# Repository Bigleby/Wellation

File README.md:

# Wellation
Solderingstation with 2 Ports for Weller RT soldering irons.

This Project is in Progress...
Status: A.0 PCBs ordered

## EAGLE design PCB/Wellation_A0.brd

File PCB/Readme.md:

Created with Eagle 7.6.0

Schematic: Wellation_A

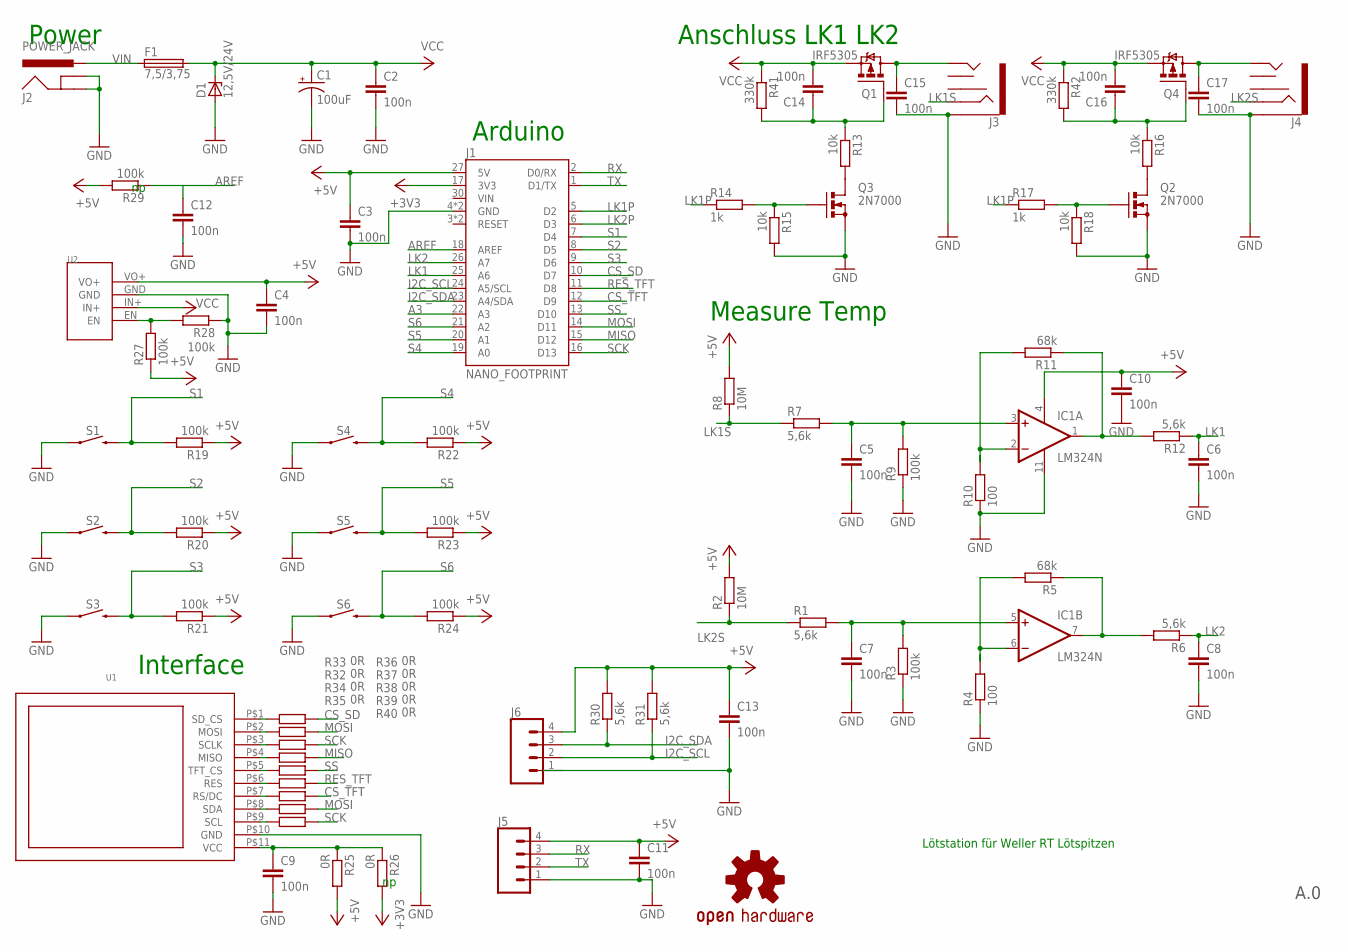
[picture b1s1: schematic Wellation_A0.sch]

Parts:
C1: 100uF; CPOL-RADIAL-2.5MM-6.5MM
C2, C3, C4, C5, C6, C7, C8, C9, C10, C11, C12, C13, C14, C15, C16, C17: 100n; C0603K
D1: 12,5V/24V; ZDIO12.5
F1: 7,5/3,75; GSH15
IC1: LM324N; DIL14
J1: NANO_FOOTPRINT; NANO
J2: POWER_JACK; POWER_JACK_PTH
J3, J4: AUDIO_JACK_3.5MM_PTH; AUDIO-JACK
J5, J6: CONN_04JST-PTH-VERT; JST-4-PTH-VERT
LOGO1: OSHW-LOGOM-COPPER; OSHW-LOGO-M_COPPER
Q1, Q4: IRF5305; TO220BV
Q2, Q3: 2N7000; SOT54E
R1, R6, R7, R12, R30, R31: 5,6k; R0603
R2, R8: 10M; R0603
R3, R9, R19, R20, R21, R22, R23, R24, R27, R28, R29: 100k; R0603
R4, R10: 100; R0603
R5, R11: 68k; R0603
R13, R15, R16, R18: 10k; R0603
R14, R17: 1k; R0603
R25, R26, R32, R33, R34, R35, R36, R37, R38, R39, R40: 0R; R0603
R41, R42: 330k; R0603
S1, S2, S3, S4, S5, S6: MOMENTARY-SWITCH-SPST-PTH-6.0MM; TACTILE_SWITCH_PTH_6.0MM
U1: TFT1800WITHSD
U2: MP2315; MP2315_MODUL

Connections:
+3V3: J1.17 (3V3), R26.2
+5V: C3.1, C4.1, C10.1, C11.1, C13.1, IC1.4 (V+), J1.27 (5V), J5.4, J6.4, R2.2, R8.2, R19.1, R20.1, R21.1, R22.1, R23.1, R24.1, R25.2, R27.1, R29.2, R30.2, R31.2, U2.VO+
A3: J1.22 (A3)
AREF: C12.1, J1.18 (AREF), R29.1
CS_SD: J1.10 (D7), R33.2
CS_TFT: J1.12 (D9), R38.2
EN: R27.2, R28.2, U2.EN
GND: C1.2 (-), C2.2, C3.2, C4.2, C5.2, C6.2, C7.2, C8.2, C9.2, C10.2, C11.2, C12.2, C13.2, C15.2, C17.2, D1.A, IC1.11 (V-), J1.4 (GND), J1.29 (GND), J2.GND, J2.GNDBREAK, J3.SLEEVE, J4.SLEEVE, J5.1, J6.1, Q2.S, Q3.S, R3.1, R4.1, R9.1, R10.1, R15.2, R18.2, R28.1, S1.1, S2.1, S3.1, S4.1, S5.1, S6.1, U1.P$10 (GND), U2.GND
I2C_SCL: J1.24 (A5/SCL), J6.2, R31.1
I2C_SDA: J1.23 (A4/SDA), J6.3, R30.1
LK1: C6.1, J1.25 (A6), R12.1
LK1P: J1.5 (D2), R14.1, R17.1
LK1PP: C15.1, J3.TIP, Q1.D
LK1PP1: C17.1, J4.TIP, Q4.D
LK1S: J3.RING, R7.1, R8.1
LK1SS: C5.1, IC1.3 (+IN), R7.2, R9.2
LK2: C8.1, J1.26 (A7), R6.1
LK2P: J1.6 (D3)
LK2S: J4.RING, R1.1, R2.1
LK2SS: C7.1, IC1.5 (+IN), R1.2, R3.2
MF1: C14.1, Q1.G, R13.1, R41.2
MF2: Q3.G, R14.2, R15.1
MF3: C16.1, Q4.G, R16.1, R42.2
MF4: Q2.G, R17.2, R18.1
MISO: J1.15 (D12), R35.2
MOSI: J1.14 (D11), R32.2, R39.2
MP1S: Q3.D, R13.2
MP2S: Q2.D, R16.2
unnamed: IC1.6 (-IN), R4.2, R5.2
unnamed: IC1.2 (-IN), R10.2, R11.2
unnamed: C9.1, R25.1, R26.1, U1.P$11 (VCC)
OP1: IC1.1 (OUT), R11.1, R12.2
OP2: IC1.7 (OUT), R5.1, R6.2
RES_TFT: J1.11 (D8), R37.2
RX: J1.2 (D0/RX), J5.3
S1: J1.7 (D4), R19.2, S1.3 (2)
S2: J1.8 (D5), R20.2, S2.3 (2)
S3: J1.9 (D6), R21.2, S3.3 (2)
S4: J1.19 (A0), R22.2, S4.3 (2)
S5: J1.20 (A1), R23.2, S5.3 (2)
S6: J1.21 (A2), R24.2, S6.3 (2)
SCK: J1.16 (D13), R34.2, R40.2
SD_CS: R33.1, U1.P$1 (SD_CS)
SD_MISO: R35.1, U1.P$4 (MISO)
SD_MOSI: R32.1, U1.P$2 (MOSI)
SD_SCK: R34.1, U1.P$3 (SCLK)
SS: J1.13 (D10), R36.2
TFT_CS: R38.1, U1.P$7 (RS/DC)
TFT_MOSI: R39.1, U1.P$8 (SDA)
TFT_RES: R37.1, U1.P$6 (RES)
TFT_SCK: R40.1, U1.P$9 (SCL)
TFT_SS: R36.1, U1.P$5 (TFT_CS)
TX: J1.1 (D1/TX), J5.2
VCC: C1.1 (+), C2.1, C14.2, C16.2, D1.C, F1.2, Q1.S, Q4.S, R41.1, R42.1, U2.IN+
VIN: F1.1, J2.PWR

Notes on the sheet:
Lötstation für Weller RT Lötspitzen
Power
Arduino
Anschluss LK1 LK2
Measure Temp
Interface
A.0

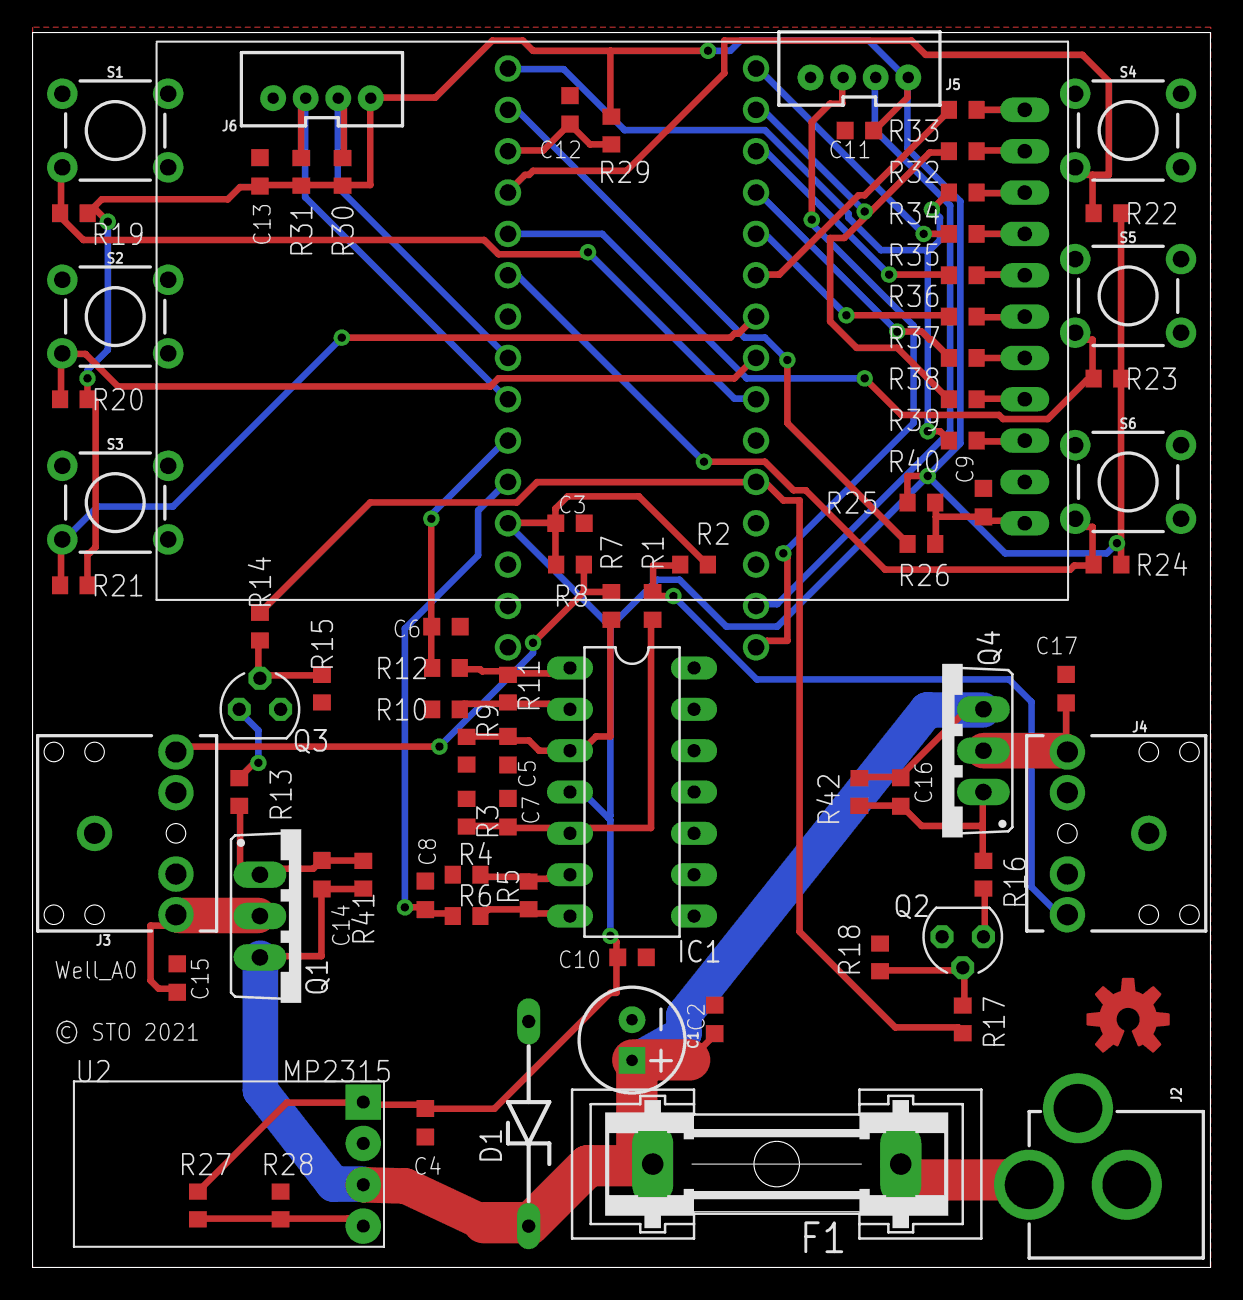
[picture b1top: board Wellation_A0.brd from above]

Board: 2 copper layers, 72.4 x 75.9 mm, 81 parts (0 on the bottom side), 53 nets.

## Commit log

2021-01-19 Create electronics
2021-01-21 Update README.md
    Update 21.01.21
2021-01-21 Initial A.0 revision
    Not tested yet

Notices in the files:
PCB/Wellation_A0.brd:
© STO 2021
parts and their libraries:
SparkFun-Capacitors: Licensing: Creative Commons ShareAlike 4.0 International - https://creativecommons.org/licenses/by-sa/4.0
